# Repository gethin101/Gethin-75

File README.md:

# Gethin-75 
A custom 75% mechanical keyboard with macro keys powered by a Raspberry pi pico and KMK firmware that I designed and built during Hackclub's Blueprint program - [project link](https://blueprint.hackclub.com/projects/12386)

I made this project to learn the fundamentals of how keyboards and macropads work, to improve my PCB design skills by learning how switch matrixes work and to get more familiar with modelling parts in CAD for 3D printing.

  <a href="#BOM">BOM</a> •
  <a href="#Images">Images</a> •
  <a href="#Firmware">Firmware</a> •
  <a href="#Full-Wiring-Table">Wiring</a> •
  <a href="#Keys">Keys</a> •
  <a href="#Stabilizers">Stabilizers</a> 

# Key Features
- **93 programmable macro keys**
- **Custom 2-layer PCB**
- **Powered by a Raspberry Pi Pico**
- **Custom KMK firmware**
- **Simple USB connectivity**
- **Clicky Cherry MX key switches**
- **3D printed case & plate**
- **Rubber feet pads for stability**
- **Easy assembly with no screws**

Demo video: [click here](https://drive.google.com/file/d/18uSU1EbHXQhmAcJua5LjIKMJpCC8aHLT/view?usp=drive_link)
  
---

 <div align="center"></div>

---

# Final Build
| Final Build | PCB |
|-------------|-----|
|  |  |
|  |  |
|  |  |

# Design Images
Here, you can see my KiCad schematic, PCB layout and 3D model of my PCB. On the right, you can see my keyboard bottom case I modelled in Fusion 360 as well as my custom plate and an assembly image.
<br>

<details>
<summary>Click to see schematic</summary>

</details>

<details>
<summary>Click to see PCB</summary>

</details>

<details>
<summary>Click to see 3D PCB</summary>

</details>

**Click any of the images below or click above to see it in more detail**

| PCB | CAD |
|-----|-----|
|  |  |
|  |  |
|  |  |

<details>
<summary>Click to see case model</summary>

</details>

<details>
<summary>Click to see plate model</summary>

</details>

<details>
<summary>Click to see keyboard assembly</summary>

</details>

 # Full Wiring Table

<details>
<summary>Click to see full wiring table</summary>
<br>

| Net   | GPIO | Notes   |
|-------|------|---------|
| ROW0  | GP2  | Matrix  |
| ROW1  | GP3  | Matrix  |
| ROW2  | GP4  | Matrix  |
| ROW3  | GP5  | Matrix  |
| ROW4  | GP6  | Matrix  |
| ROW5  | GP7  | Matrix  |
| COL0  | GP8  | Matrix  |
| COL1  | GP9  | Matrix  |
| COL2  | GP10 | Matrix  |
| COL3  | GP11 | Matrix  |
| COL4  | GP12 | Matrix  |
| COL5  | GP13 | Matrix  |
| COL6  | GP14 | Matrix  |
| COL7  | GP15 | Matrix  |
| COL8  | GP16 | Matrix  |
| COL9  | GP17 | Matrix  |
| COL10 | GP18 | Matrix  |
| COL11 | GP19 | Matrix  |
| COL12 | GP20 | Matrix  |
| COL13 | GP21 | Matrix  |
| COL14 | GP22 | Matrix  |
| COL15 | GP26 | Matrix  |
| COL16 | GP27 | Matrix  |
| 3V3   | +3v3 | Pico    |
| GND   | GND  | Common  |

</details>

# Firmware
I have written my custom keyboard code in CircuitPython using KMK to control the keystrokes and I have made a macro handler at the start that means I can change the function of any of my keys whenever I want.

My macro keys at the moment:
- Previous song
- Play / Pause
- Next song
- Volume down
- Volume up
- Lock
- File Explorer
- Task Manager

**Setup:**
- Flash [CircuitPython](/Firmware/adafruit-circuitpython-raspberry_pi_pico2-en_GB-10.1.3.uf2) onto the pico
- Download KMK from [Github](/Firmware/kmk) and copy to root
- Import [code.py](/Firmware/code.py) onto the pico using Thonny

# Keys
My keyboard is a 75% keyboard with a total of 93 keys - 85 normal and 8 custom macro keys.

Here is the link to my custom [keyboard layout](https://www.keyboard-layout-editor.com/#/gists/a3df558aee879b924d336356534e8c5d) <br>

---

# BOM
| Qty | Item | Notes | Cost (£) | USD ($) | Link |
|------|-----|-------|----------|---------|------|
| 100 | MX-Style key switches | Black 100pcs | £21.49 | $28.68 | [AE](https://www.aliexpress.com/item/1005006091988869.html?spm=a2g0o.productlist.main.7.75c58gJx8gJxPL&algo_pvid=9ce49efa-7e7f-4084-9907-27c06cf10fb0&algo_exp_id=9ce49efa-7e7f-4084-9907-27c06cf10fb0-6&pdp_ext_f=%7B%22order%22%3A%22835%22%2C%22spu_best_type%22%3A%22price%22%2C%22eval%22%3A%221%22%2C%22fromPage%22%3A%22search%22%7D&pdp_npi=6%40dis%21GBP%214.28%210.75%21%21%2138.69%216.78%21%40211b613917718647541901282e256e%2112000035698597722%21sea%21UK%210%21ABX%211%210%21n_tag%3A-29910%3Bd%3Ac7b67d0a%3Bm03_new_user%3A-29895%3BpisId%3A5000000197842856&curPageLogUid=NyDkJsY5AIXg&utparam-url=scene%3Asearch%7Cquery_from%3A%7Cx_object_id%3A1005006091988869%7C_p_origin_prod%3A)
| 126 | Cherry MX Key caps | Yunhu White | £5.49 | $7.33 | [AE](https://www.aliexpress.com/item/1005007321700850.html) |
| 1 | Raspberry Pi Pico | USB C | £1.93 | $2.58 | [AE](https://www.aliexpress.com/item/1005006054409042.html) |
| 5 | Plate-mount stabilizers | 4x 2u and 6.25u | £4.29 | $5.79 | [AE](https://www.aliexpress.com/item/1005002552011081.html?spm=a2g0o.detail.similar_items.1.74c544gP44gPGi&utparam-url=scene%3Aimage_search%7Cquery_from%3Adetail_bigimg%7Cx_object_id%3A1005002552011081%7C_p_origin_prod%3A&algo_pvid=5eb5f0e8-483f-4e53-bf91-23823326ba18&algo_exp_id=5eb5f0e8-483f-4e53-bf91-23823326ba18&pdp_ext_f=%7B%22order%22%3A%229%22%2C%22fromPage%22%3A%22search%22%7D&pdp_npi=6%40dis%21GBP%215.64%214.29%21%21%217.36%215.60%21%40211b655217724376724172627e1aeb%2112000021107331951%21sea%21UK%210%21ABX%211%210%21n_tag%3A-29910%3Bd%3Ac7b67d0a%3Bm03_new_user%3A-29895) |
| 100 | 1N4148 diodes | Through-hole | £0.89 | $1.19 | [AE](https://www.aliexpress.com/item/4001126137167.html?spm=a2g0o.productlist.main.1.90b1o1uho1uh6B&algo_pvid=c367e696-c97b-45f9-aadc-442c0813800d&algo_exp_id=c367e696-c97b-45f9-aadc-442c0813800d-0&pdp_ext_f=%7B%22order%22%3A%221197%22%2C%22eval%22%3A%221%22%2C%22fromPage%22%3A%22search%22%7D&pdp_npi=6%40dis%21GBP%210.89%210.76%21%21%211.16%210.99%21%402103894417717723958752301e1008%2110000014629985518%21sea%21UK%210%21ABX%211%210%21n_tag%3A-29910%3Bd%3Ac7b67d0a%3Bm03_new_user%3A-29895%3BpisId%3A5000000197842856&curPageLogUid=KHdyO7FyLrgo&utparam-url=scene%3Asearch%7Cquery_from%3A%7Cx_object_id%3A4001126137167%7C_p_origin_prod%3A) |
| 50 | Rubber feet pads | 13x5.5mm | £0.76 | $1.02 | [AE](https://www.aliexpress.com/item/1005006832476105.html) |
| 5 | Custom PCB | Gerber quote | £14.37 | $19.22 | [JLCPCB]([https://www.aliexpress.com/item/1005006832476105.html](https://jlcpcb.com/)) |
| 2 | 3D Print case and plate | #printing-legion (estimate) | £8 | $10.68 | [N/A](www.github.com/gethin101) |
| 0 | Shipping (will refund if extra) | Told to put this | £10 | $13.37 | [Slack](https://hackclub.enterprise.slack.com/archives/C083P4FJM46) |
| **390** | **Total cost:** | **May vary slightly** | **£70.69** | **$94.49** | [BOM](/Bom.csv) |

# Cart Screenshots

<details>
<summary>Click to expand cart screenshots</summary>

</details>

# Stabilizers 

My spacebar, left shift, right shift, enter and backspace all need MX stabilizers as they are above 2u and these will be plate-mounted.

| Key | Size | Stabilizer |
|-----|------|------------|
|Space| 6.25u| 6.25u plate-mount |
|R-Shift| 2.75u | 2u plate-mount |
|Enter | 2.25u | 2u plate-mount |
|Backspace | 2u | 2u plate-mount |

---

---

# Blueprint requirements

- [✅] A short description of what your project is  
- [✅] A couple of sentences on how to use your project  
- [✅] A couple of sentences on why you made the project  

- [✅ ] Screenshot of a full 3D model of your project  
- [✅ ] Screenshot of your PCB (if applicable)  
- [✅ ] Wiring diagram (if any wiring is not on a PCB)  
- [✅] Bill of Materials (BOM) in table format at the end of the README, with links [BOM](/BOM.csv)

- [✅] Fully original, customized design (not a direct copy of any guide)  
- [✅] Complete CAD assembly including all components (electronics included)  
- [✅] Firmware present (even if untested)  
- [✅] Design sanity‑checked with someone else  [(checked by @krunch)](https://hackclub.enterprise.slack.com/team/U0828MFCD99) + preliminary approved by [@shadow](https://hackclub.enterprise.slack.com/team/U09V9HPQAMD)

- [✅] BOM in CSV format in the root directory, with links  
- [✅] PCB source files (.kicad_pro, .kicad_sch, gerbers.zip, etc.) if applicable  
- [✅] A .STEP file of the full 3D CAD model including electronics  
- [✅] Source CAD files (.f3d, .FCStd, etc., or OnShape public link in README)  
- [✅] All other project files included (firmware, libraries, references, etc.)  
- [✅] Repository organized into readable, logical folders  

> ⚠️ **Important:** Missing a complete .STEP file with all electronics and CAD will result in project rejection. ✅

Designed and built by [@gethin101](https://github.com/gethin101)

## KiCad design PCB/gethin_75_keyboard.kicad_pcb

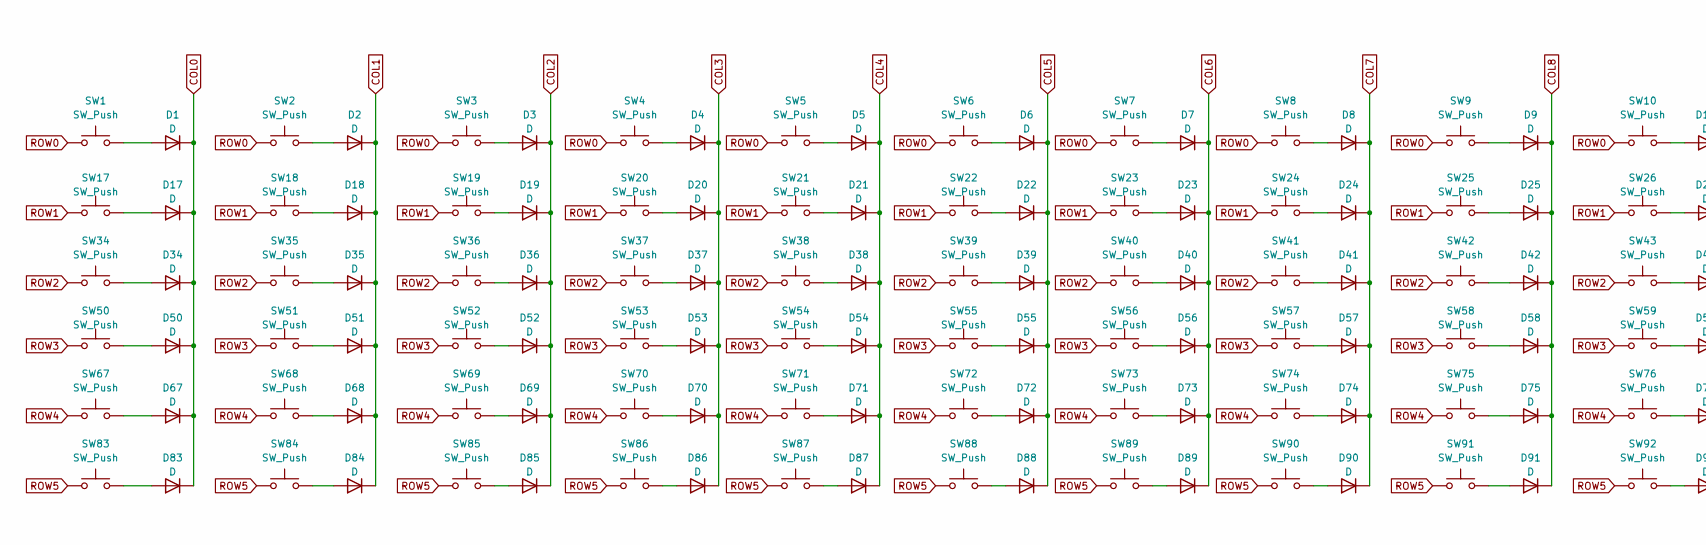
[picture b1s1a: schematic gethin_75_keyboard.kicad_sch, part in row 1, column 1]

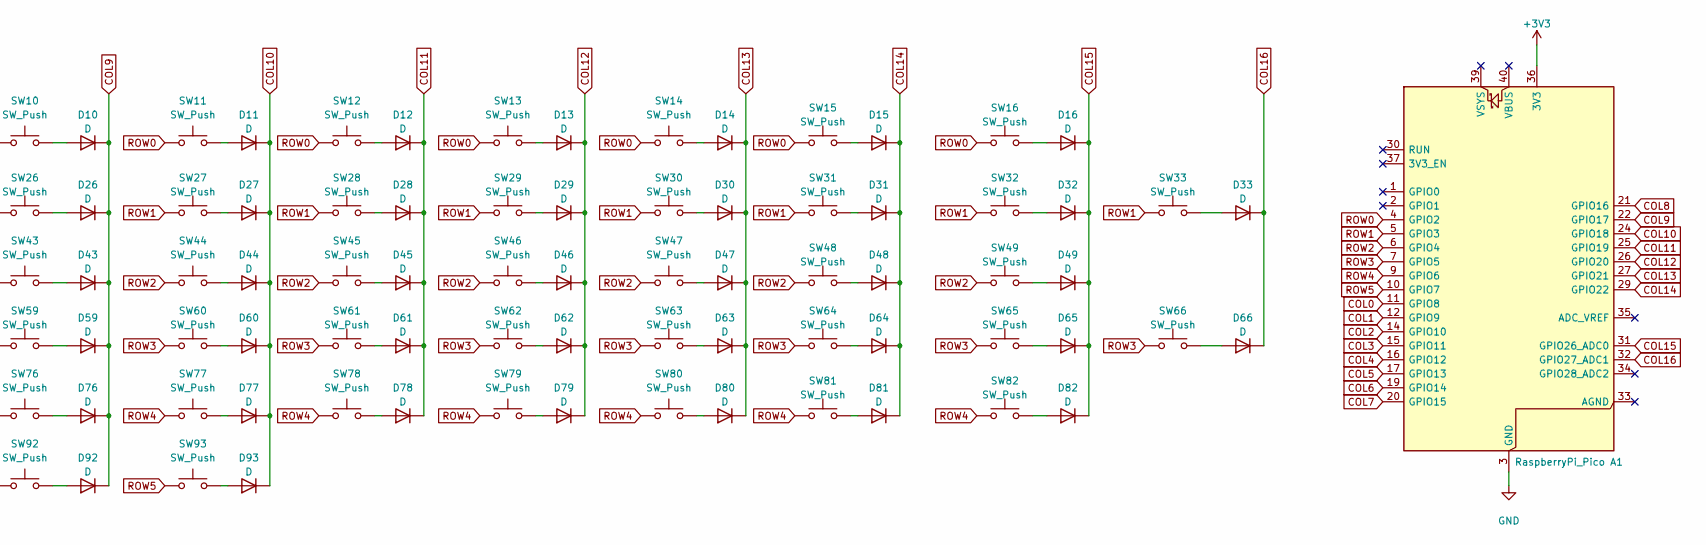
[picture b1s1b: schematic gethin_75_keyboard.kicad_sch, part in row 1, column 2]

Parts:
A1: RaspberryPi_Pico; RaspberryPi_Pico_SMD_HandSolder
D1, D2, D3, D4, D5, D6, D7, D8, D9, D10, D11, D12, D13, D14, D15, D16, D17, D18, D19, D20, D21, D22, D23, D24, D25, D26, D27, D28, D29, D30, D31, D32, D33, D34, D35, D36, D37, D38, D39, D40, D41, D42, D43, D44, D45, D46, D47, D48, D49, D50, D51, D52, D53, D54, D55, D56, D57, D58, D59, D60, D61, D62, D63, D64, D65, D66, D67, D68, D69, D70, D71, D72, D73, D74, D75, D76, D77, D78, D79, D80, D81, D82, D83, D84, D85, D86, D87, D88, D89, D90, D91, D92, D93: D; D_DO-35_SOD27_P7.62mm_Horizontal
SW1, SW2, SW3, SW4, SW5, SW6, SW7, SW8, SW9, SW10, SW11, SW12, SW13, SW14, SW15, SW16, SW17, SW18, SW19, SW20, SW21, SW22, SW23, SW24, SW25, SW26, SW27, SW28, SW29, SW31, SW32, SW33, SW34, SW35, SW36, SW37, SW38, SW39, SW40, SW41, SW42, SW43, SW44, SW45, SW46, SW47, SW48, SW49, SW51, SW52, SW53, SW54, SW55, SW56, SW57, SW58, SW59, SW60, SW61, SW62, SW64, SW65, SW66, SW67, SW68, SW69, SW70, SW71, SW72, SW73, SW74, SW75, SW76, SW77, SW78, SW80, SW81, SW82, SW91, SW92, SW93: SW_Push; SW_Cherry_MX_1.00u_Plate
SW30: SW_Push; SW_Cherry_MX_2.00u_Plate
SW50: SW_Push; SW_Cherry_MX_1.75u_Plate
SW63: SW_Push; SW_Cherry_MX_2.25u_Plate
SW79: SW_Push; SW_Cherry_MX_2.75u_Plate
SW83, SW84, SW85, SW87, SW88, SW89, SW90: SW_Push; SW_Cherry_MX_1.25u_Plate
SW86: SW_Push; SW_Cherry_MX_6.25u_Plate

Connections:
+3V3: A1.36 (3V3)
COL0: A1.11 (GPIO8), D1.1 (K), D17.1 (K), D34.1 (K), D50.1 (K), D67.1 (K), D83.1 (K)
COL1: A1.12 (GPIO9), D2.1 (K), D18.1 (K), D35.1 (K), D51.1 (K), D68.1 (K), D84.1 (K)
COL2: A1.14 (GPIO10), D3.1 (K), D19.1 (K), D36.1 (K), D52.1 (K), D69.1 (K), D85.1 (K)
COL3: A1.15 (GPIO11), D4.1 (K), D20.1 (K), D37.1 (K), D53.1 (K), D70.1 (K), D86.1 (K)
COL4: A1.16 (GPIO12), D5.1 (K), D21.1 (K), D38.1 (K), D54.1 (K), D71.1 (K), D87.1 (K)
COL5: A1.17 (GPIO13), D6.1 (K), D22.1 (K), D39.1 (K), D55.1 (K), D72.1 (K), D88.1 (K)
COL6: A1.19 (GPIO14), D7.1 (K), D23.1 (K), D40.1 (K), D56.1 (K), D73.1 (K), D89.1 (K)
COL7: A1.20 (GPIO15), D8.1 (K), D24.1 (K), D41.1 (K), D57.1 (K), D74.1 (K), D90.1 (K)
COL8: A1.21 (GPIO16), D9.1 (K), D25.1 (K), D42.1 (K), D58.1 (K), D75.1 (K), D91.1 (K)
COL9: A1.22 (GPIO17), D10.1 (K), D26.1 (K), D43.1 (K), D59.1 (K), D76.1 (K), D92.1 (K)
COL10: A1.24 (GPIO18), D11.1 (K), D27.1 (K), D44.1 (K), D60.1 (K), D77.1 (K), D93.1 (K)
COL11: A1.25 (GPIO19), D12.1 (K), D28.1 (K), D45.1 (K), D61.1 (K), D78.1 (K)
COL12: A1.26 (GPIO20), D13.1 (K), D29.1 (K), D46.1 (K), D62.1 (K), D79.1 (K)
COL13: A1.27 (GPIO21), D14.1 (K), D30.1 (K), D47.1 (K), D63.1 (K), D80.1 (K)
COL14: A1.29 (GPIO22), D15.1 (K), D31.1 (K), D48.1 (K), D64.1 (K), D81.1 (K)
COL15: A1.31 (GPIO26_ADC0), D16.1 (K), D32.1 (K), D49.1 (K), D65.1 (K), D82.1 (K)
COL16: A1.32 (GPIO27_ADC1), D33.1 (K), D66.1 (K)
GND: A1.3 (GND), A1.8 (GND), A1.13 (GND), A1.18 (GND), A1.23 (GND), A1.28 (GND), A1.38 (GND)
unnamed: D1.2 (A), SW1.2
unnamed: D2.2 (A), SW2.2
unnamed: D3.2 (A), SW3.2
unnamed: D4.2 (A), SW4.2
unnamed: D5.2 (A), SW5.2
unnamed: D6.2 (A), SW6.2
unnamed: D7.2 (A), SW7.2
unnamed: D8.2 (A), SW8.2
unnamed: D9.2 (A), SW9.2
unnamed: D10.2 (A), SW10.2
unnamed: D11.2 (A), SW11.2
unnamed: D12.2 (A), SW12.2
unnamed: D13.2 (A), SW13.2
unnamed: D14.2 (A), SW14.2
unnamed: D15.2 (A), SW15.2
unnamed: D16.2 (A), SW16.2
unnamed: D17.2 (A), SW17.2
unnamed: D18.2 (A), SW18.2
unnamed: D19.2 (A), SW19.2
unnamed: D20.2 (A), SW20.2
unnamed: D21.2 (A), SW21.2
unnamed: D22.2 (A), SW22.2
unnamed: D23.2 (A), SW23.2
unnamed: D24.2 (A), SW24.2
unnamed: D25.2 (A), SW25.2
unnamed: D26.2 (A), SW26.2
unnamed: D27.2 (A), SW27.2
unnamed: D28.2 (A), SW28.2
unnamed: D29.2 (A), SW29.2
unnamed: D30.2 (A), SW30.2
unnamed: D31.2 (A), SW31.2
unnamed: D32.2 (A), SW32.2
unnamed: D33.2 (A), SW33.2
unnamed: D34.2 (A), SW34.2
unnamed: D35.2 (A), SW35.2
unnamed: D36.2 (A), SW36.2
unnamed: D37.2 (A), SW37.2
unnamed: D38.2 (A), SW38.2
unnamed: D39.2 (A), SW39.2
unnamed: D40.2 (A), SW40.2
unnamed: D41.2 (A), SW41.2
unnamed: D42.2 (A), SW42.2
unnamed: D43.2 (A), SW43.2
unnamed: D44.2 (A), SW44.2
unnamed: D45.2 (A), SW45.2
unnamed: D46.2 (A), SW46.2
unnamed: D47.2 (A), SW47.2
unnamed: D48.2 (A), SW48.2
unnamed: D49.2 (A), SW49.2
unnamed: D50.2 (A), SW50.2
unnamed: D51.2 (A), SW51.2
unnamed: D52.2 (A), SW52.2
unnamed: D53.2 (A), SW53.2
unnamed: D54.2 (A), SW54.2
unnamed: D55.2 (A), SW55.2
unnamed: D56.2 (A), SW56.2
unnamed: D57.2 (A), SW57.2
unnamed: D58.2 (A), SW58.2
unnamed: D59.2 (A), SW59.2
unnamed: D60.2 (A), SW60.2
unnamed: D61.2 (A), SW61.2
unnamed: D62.2 (A), SW62.2
unnamed: D63.2 (A), SW63.2
unnamed: D64.2 (A), SW64.2
unnamed: D65.2 (A), SW65.2
unnamed: D66.2 (A), SW66.2
unnamed: D67.2 (A), SW67.2
unnamed: D68.2 (A), SW68.2
unnamed: D69.2 (A), SW69.2
unnamed: D70.2 (A), SW70.2
unnamed: D71.2 (A), SW71.2
unnamed: D72.2 (A), SW72.2
unnamed: D73.2 (A), SW73.2
unnamed: D74.2 (A), SW74.2
unnamed: D75.2 (A), SW75.2
unnamed: D76.2 (A), SW76.2
unnamed: D77.2 (A), SW77.2
unnamed: D78.2 (A), SW78.2
unnamed: D79.2 (A), SW79.2
unnamed: D80.2 (A), SW80.2
unnamed: D81.2 (A), SW81.2
unnamed: D82.2 (A), SW82.2
unnamed: D83.2 (A), SW83.2
unnamed: D84.2 (A), SW84.2
unnamed: D85.2 (A), SW85.2
unnamed: D86.2 (A), SW86.2
unnamed: D87.2 (A), SW87.2
unnamed: D88.2 (A), SW88.2
unnamed: D89.2 (A), SW89.2
unnamed: D90.2 (A), SW90.2
unnamed: D91.2 (A), SW91.2
unnamed: D92.2 (A), SW92.2
unnamed: D93.2 (A), SW93.2
ROW0: A1.4 (GPIO2), SW1.1, SW2.1, SW3.1, SW4.1, SW5.1, SW6.1, SW7.1, SW8.1, SW9.1, SW10.1, SW11.1, SW12.1, SW13.1, SW14.1, SW15.1, SW16.1
ROW1: A1.5 (GPIO3), SW17.1, SW18.1, SW19.1, SW20.1, SW21.1, SW22.1, SW23.1, SW24.1, SW25.1, SW26.1, SW27.1, SW28.1, SW29.1, SW30.1, SW31.1, SW32.1, SW33.1
ROW2: A1.6 (GPIO4), SW34.1, SW35.1, SW36.1, SW37.1, SW38.1, SW39.1, SW40.1, SW41.1, SW42.1, SW43.1, SW44.1, SW45.1, SW46.1, SW47.1, SW48.1, SW49.1
ROW3: A1.7 (GPIO5), SW50.1, SW51.1, SW52.1, SW53.1, SW54.1, SW55.1, SW56.1, SW57.1, SW58.1, SW59.1, SW60.1, SW61.1, SW62.1, SW63.1, SW64.1, SW65.1, SW66.1
ROW4: A1.9 (GPIO6), SW67.1, SW68.1, SW69.1, SW70.1, SW71.1, SW72.1, SW73.1, SW74.1, SW75.1, SW76.1, SW77.1, SW78.1, SW79.1, SW80.1, SW81.1, SW82.1
ROW5: A1.10 (GPIO7), SW83.1, SW84.1, SW85.1, SW86.1, SW87.1, SW88.1, SW89.1, SW90.1, SW91.1, SW92.1, SW93.1

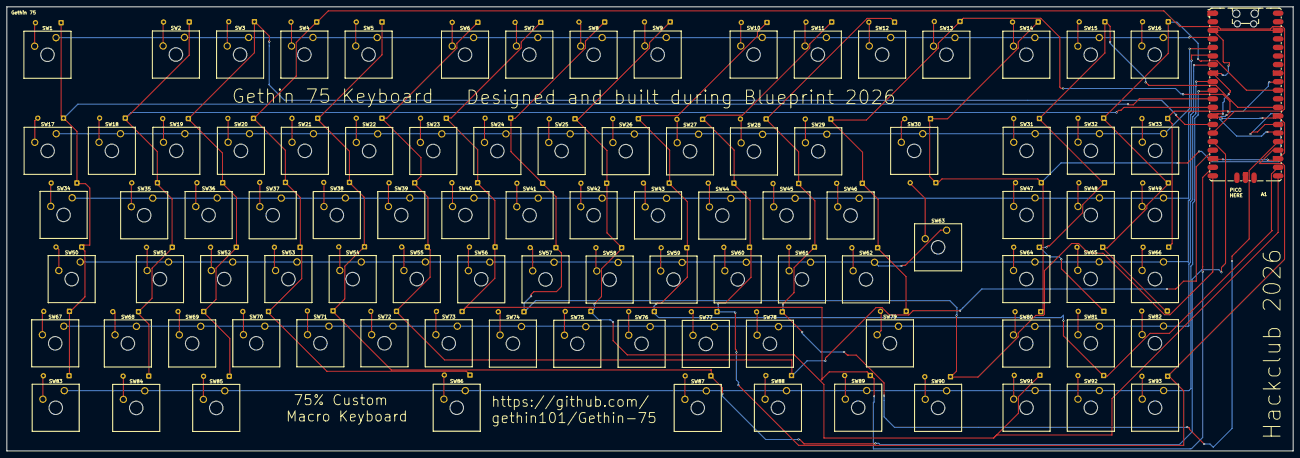
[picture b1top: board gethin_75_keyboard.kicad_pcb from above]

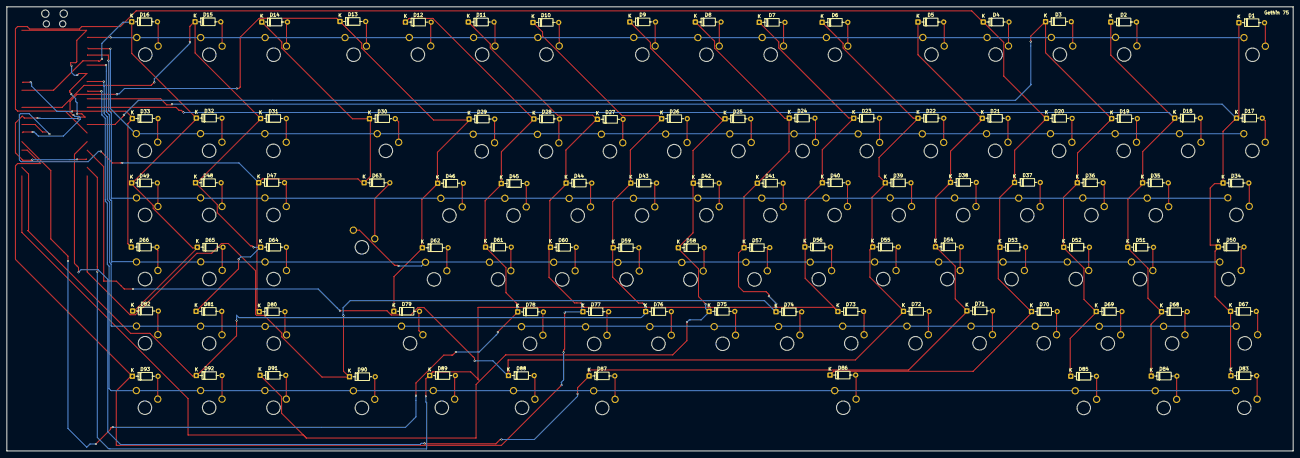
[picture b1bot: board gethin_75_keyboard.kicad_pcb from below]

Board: 2 copper layers, 381.7 x 131.8 mm, 187 parts (93 on the bottom side), 117 nets.

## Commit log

2026-03-02 Rename Screenshot 2026-03-02 074159.png to pcb_cart.png
2026-03-02 Create j
2026-03-02 Rename Screenshot 2026-03-02 075330.png to cart_2.png
2026-03-02 Rename Screenshot 2026-03-02 075320.png to cart_1.png
2026-03-02 Rename Screenshot 2026-03-02 075451.png to cart_pi.png
2026-03-02 Rename Screenshot 2026-03-02 080551.png to cart_1.png
2026-03-02 Rename Screenshot 2026-03-02 080655.png to cart_2.png
2026-03-02 Rename Screenshot 2026-03-02 080651.png to cart_1.png
2026-03-02 Rename Screenshot 2026-03-02 080655.png to ali_1.png
2026-03-02 Rename ali_1.png to ali_2.png
2026-03-02 Rename Screenshot 2026-03-02 080651.png to ali_1.png
2026-03-02 Create 1
2026-03-04 Rename Screenshot 2026-03-04 072834.png to schem.png
2026-03-04 Rename BOM.md to BOM.csv
2026-03-04 Rename BOM.csv to BOM.md
2026-03-04 Rename BOM.md to assets/BOM.md
2026-03-04 Rename Screenshot 2026-03-04 154513.png to cart_pcb.png
2026-03-04 Rename ali_1 (1).png to cart/aliExpress1.png
2026-03-04 Rename ali_2 (1).png to cart/aliExpress2.png
2026-03-04 Rename cart_pcb (2).png to cart/PCB.png
2026-04-14 Create 0
2026-04-14 Rename IMG_3211.jpeg to 2.jpeg
2026-04-14 Rename IMG_3202.jpeg to 3.jpeg
2026-04-14 Rename IMG_3215.jpg to 1.jpg
2026-04-14 Rename IMG_3131.jpeg to 5.jpeg
2026-04-14 Rename IMG_3135.jpeg to 4.jpeg
2026-04-14 Rename IMG_3197.jpeg to 6.jpeg
2026-04-14 Rename IMG_3209 (1).jpeg to 7.jpeg
2026-04-14 Rename IMG_3202 (1).jpeg to 8.jpeg
